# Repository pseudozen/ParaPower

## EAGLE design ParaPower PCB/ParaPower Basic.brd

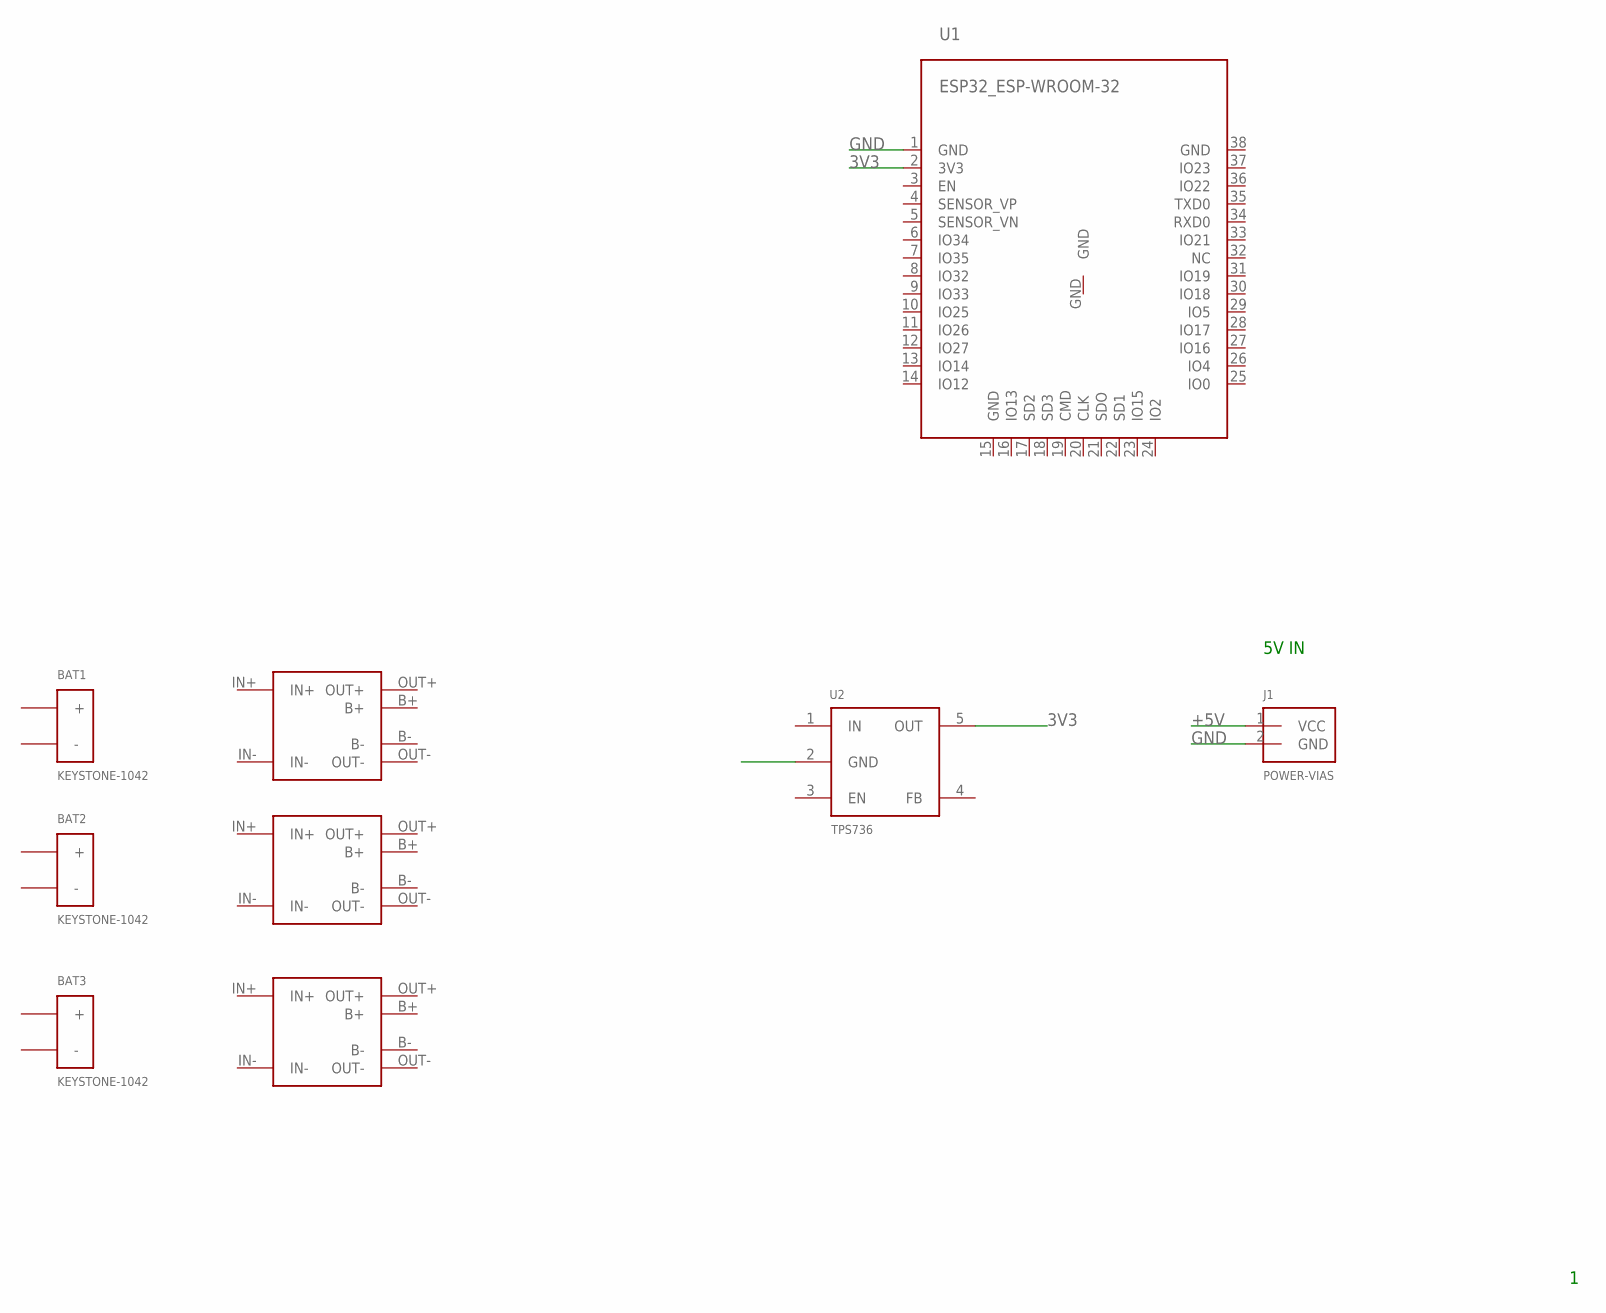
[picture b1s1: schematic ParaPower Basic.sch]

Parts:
BAT1, BAT2, BAT3: KEYSTONE-1042; KEYSTONE_1042
J1: POWER-VIAS; 2CT-VIAS
U1: ESP32_ESP-WROOM-32
U2: TPS736; SOT23-5L
U$1, U$2, U$3: TP4056-MODULE; TP4056-LITHIUM-PROTECTED-MODULE

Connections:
3V3: U1.2 (3V3), U2.5 (OUT)
+: BAT1.1 (+), BAT2.1 (+), BAT3.1 (+)
+5V: J1.1 (VCC)
-: BAT1.2 (-), BAT2.2 (-), BAT3.2 (-)
B+: U$1.B+, U$2.B+, U$3.B+
B-: U$1.B-, U$2.B-, U$3.B-
GND: J1.2 (GND), U1.1 (GND), U2.2 (GND)
IN: U2.1 (IN)
IN+: U$1.IN+, U$2.IN+, U$3.IN+
IN-: U$1.IN-, U$2.IN-, U$3.IN-
OUT+: U$1.OUT+, U$2.OUT+, U$3.OUT+
OUT-: U$1.OUT-, U$2.OUT-, U$3.OUT-

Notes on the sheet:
5V IN

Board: 2 copper layers, 9 parts (0 on the bottom side), 10 nets, no tracks yet.

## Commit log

2019-02-14 added initial files, sized for PolyCase ML-46f-1508 enclosure
2019-02-14 started to add voltage regulation section
2019-02-14 started to modify board layout for footprint of enclosure
